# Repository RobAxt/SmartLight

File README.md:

# SmartLight :bulb:

Smart Light based on Homie-ESP8266 and Wemos D1 Mini with the Relay Shield

**GPIO:**
* D1: output - To Relay.
* D2: input - From Toggle Button to Locally Toggle Light.
* D3: input - Homie Reset Config.
* D4: output - Homie Status Led.

**Power:** 
* Hi-Link P/N: HLK-5M05

**Hardware Build V2** :construction:
* [Photos](https://photos.app.goo.gl/Z1Gv3g5B6ht62BdJ8)

**3D Design** :construction:
* [TinkerCad](https://www.tinkercad.com/things/h2CH0p7LDbv-relaisbox)

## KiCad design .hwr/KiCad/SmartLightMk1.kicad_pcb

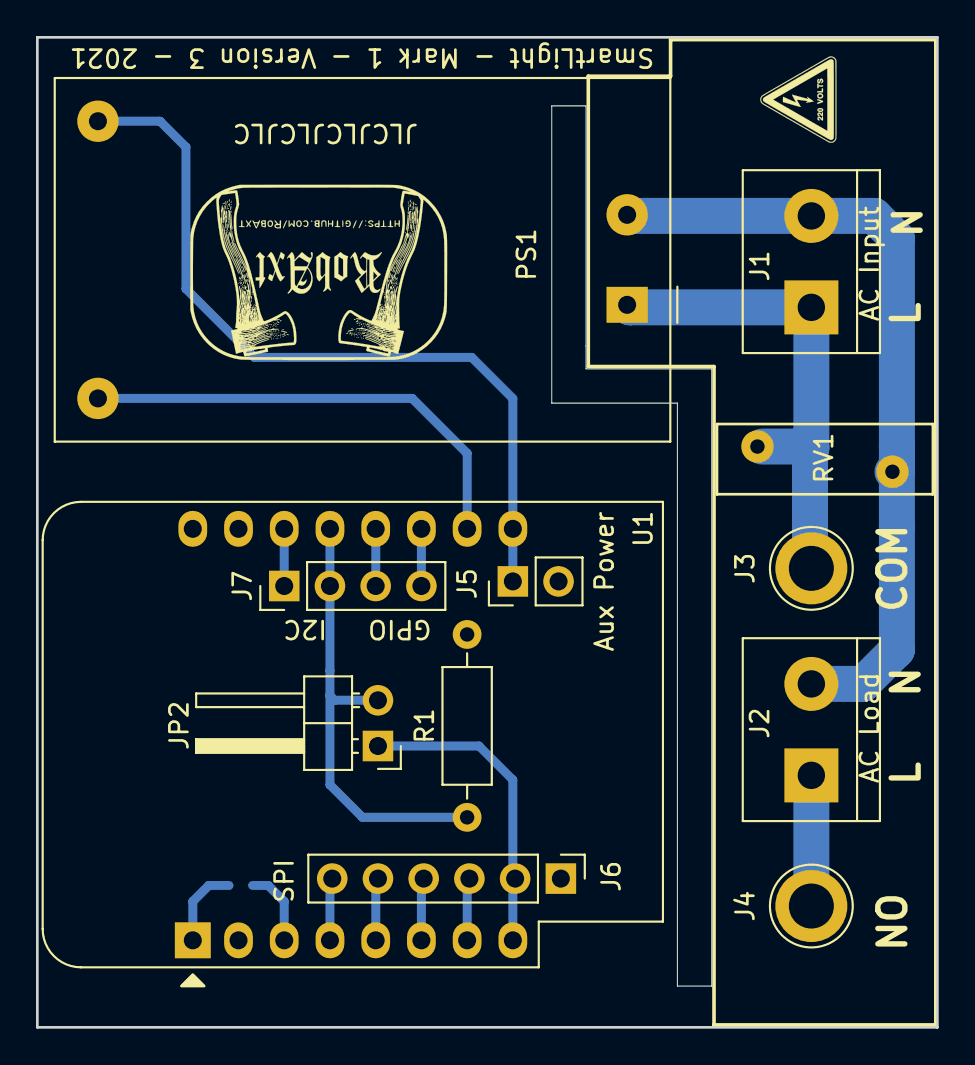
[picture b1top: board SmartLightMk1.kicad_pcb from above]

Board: 2 copper layers, 50.0 x 55.0 mm, 13 parts (1 on the bottom side), 16 nets.

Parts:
J1: AC Input; TerminalBlock_bornier-2_P5.08mm
J2: AC Load; TerminalBlock_bornier-2_P5.08mm
J3: Relay COM; TestPoint_Loop_D3.80mm_Drill2.5mm
J4: Relay NO; TestPoint_Loop_D3.80mm_Drill2.5mm
J5: Aux Power; PinHeader_1x02_P2.54mm_Vertical
J6: SPI; PinHeader_1x06_P2.54mm_Vertical
J7: GPIO I2C; PinHeader_1x04_P2.54mm_Vertical
JP1: Sleep; SolderJumper-2_P1.3mm_Open_RoundedPad1.0x1.5mm
JP2: Jumper_NO_Small; PinHeader_1x02_P2.54mm_Horizontal
PS1: HLK-PM01; Converter_ACDC_HiLink_HLK-PMxx
R1: R; R_Axial_DIN0207_L6.3mm_D2.5mm_P10.16mm_Horizontal
RV1: Varistor; RV_Disc_D12mm_W3.9mm_P7.5mm
U1: WeMos_D1_mini; WEMOS_D1_mini_light

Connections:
+3V3: J6.2, JP2.1, U1.8
+5V: J5.1, PS1.4, U1.9
D0: JP1.1, U1.3
D1: J7.1, U1.14
D2: J7.2, JP2.2, R1.1, U1.13
D3: J7.3, U1.12
D4: J7.4, U1.11
D5: J6.6, U1.4
D6: J6.5, U1.5
D7: J6.4, U1.6
D8: J6.3, U1.7
GND: J5.2, J6.1, PS1.3, R1.2, U1.10
unnamed: J1.1, J3.1, PS1.1, RV1.1
unnamed: J1.2, J2.2, PS1.2, RV1.2
unnamed: J2.1, J4.1
unnamed: JP1.2, U1.1

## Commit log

2020-02-18 Update interruptExample.cpp
    Modifing include line
2020-02-22 Fist Compile....
2020-02-22 adding files
2020-03-10 Update README.md
    MIT License.
2020-03-17 Firsts succesfull tests...
2020-03-17 Firsts Test succesful
2020-03-22 Release Ver. 1.1.1
2020-03-22 Homie Ver Update to a22f7e3
2020-03-30 Delete config.json
    Private info
2020-03-31 library updates
2020-04-13 update .gitignore file
2020-04-13 updating .gitignore file
2020-05-28 Ver.1.1.2 - Switch interrupt enhanced debounce.
2020-06-09 Adding remote logging using TelnetSream.
2020-11-11 using Bounce2 library to handle input
2021-08-20 Hardware Files Sent to Production.
2021-09-21 bounce library usage updated
2021-09-23 Adding Syslog and Homie Update.

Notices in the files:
README.md:
License: MIT License
